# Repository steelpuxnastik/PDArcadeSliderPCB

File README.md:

# PDArcadeSliderPCB
PCB of slider for a homemade arcade controller.
First version of slider PCB (without ground hatching)

Second version with ground hatching and other modifications (because first you had to read the instructions, and then do).

Sorry, I forget to make photoes of last at this moment (third) version of PCB, because it's already installed to controller and working perfectly, so I like it :)))

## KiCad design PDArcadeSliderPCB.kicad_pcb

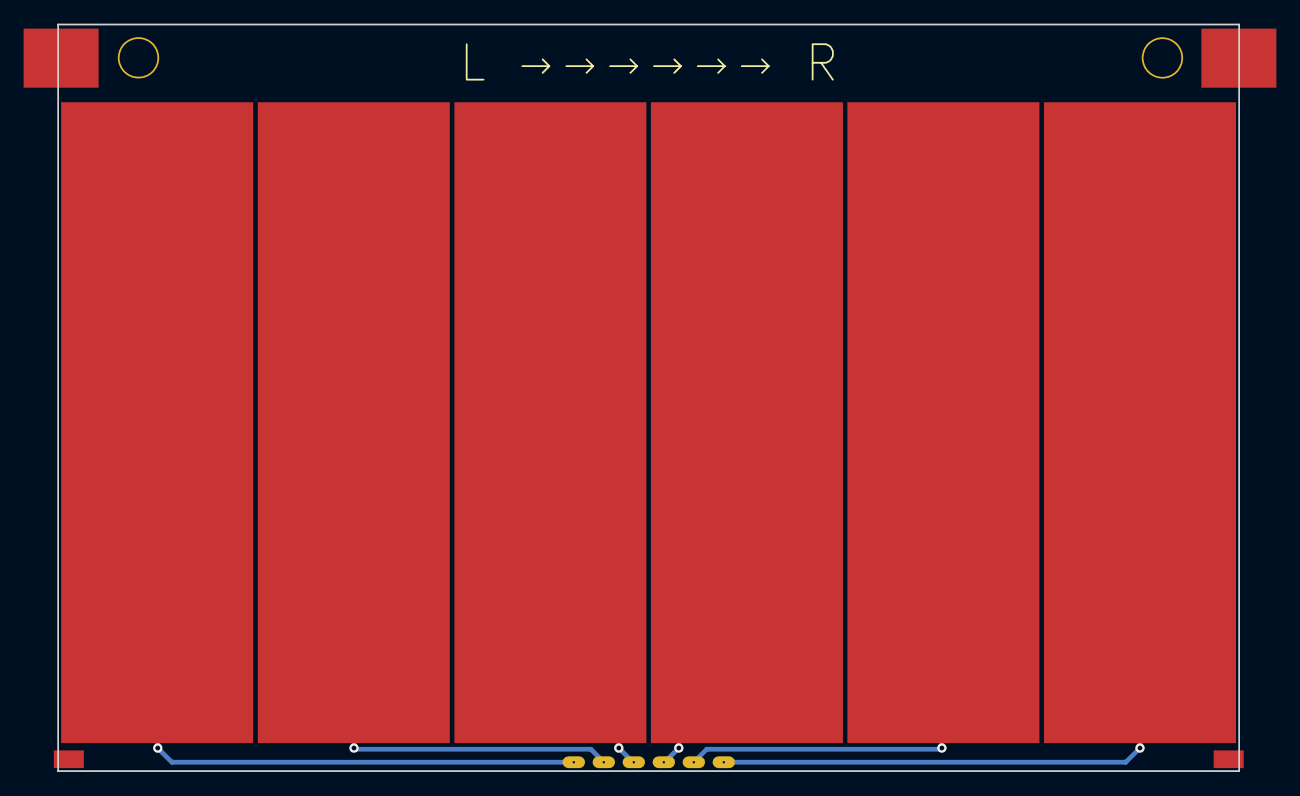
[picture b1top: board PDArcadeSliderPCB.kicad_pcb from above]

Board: 2 copper layers, 100.0 x 63.2 mm, 7 parts (1 on the bottom side), 6 nets.

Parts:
J2: Conn_01x06_Male; testtt
U1, U2, U3, U4, U5, U6: testsensorg; sensorg

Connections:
unnamed: J2.1, U1.1
unnamed: J2.2, U4.1
unnamed: J2.3, U2.1
unnamed: J2.4, U5.1
unnamed: J2.5, U3.1
unnamed: J2.6, U6.1

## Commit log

2019-11-26 Changes to my settings of slider
2019-11-28 some changes for beauty
2019-12-10 Added ground hatching to PCB
    Added ground hatching to PCB to decrease parasitic capacitance
2019-12-11 Improved hatching
2019-12-12 Changed to 7 mil ground hatching and additional free-standing vias
    Changed to 7 mil ground hatching and additional free-standing vias if big holes will be destroyed by screw after mounting to panel
2019-12-14 Trying to find better hatching settings
2019-12-15 Ground hatching from old manual
    Ground hatching from old manual
    https://forum.kicad.info/t/copper-pour-with-hatched-fill-instead-of-solid-fill/860/8
    because for now KiCad cannot make hatching like this
2019-12-16 Changed through holes on CapSense traces. Sent to production
    Changed through holes on CapSense traces. Sent to production
2019-12-30 images of first version of slider
2020-02-11 images
2020-02-19 Version with ground hatching failed. Changes and fixes
    without ground hatching
2020-02-20 little bigger pads, deleted trash
2020-03-05 Changes, sent to production
2020-05-25 Changed drill size of mounting points to smaller
